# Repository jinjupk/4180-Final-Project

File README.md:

# Contactless Car Unlocking System [ECE 4180 Final Project]

Georgia Institute of Technology \
ECE 4180 (Embedded Systems Design)

Pearl Park \
Lawrence Ro \
Swarna Shah 

## Overview

The Contactless Car Unlocking System allows a user to unlock a car with a specific NFC card instead of using a physical key. In the following demonstration, a Buzzcard student ID is scanned at the sensor location to remotely press the unlock button inside of the car using a 5V relay. The system is powered by the car’s battery which is stepped down to a low enough voltage with a voltage regulator. All components are interfaced through a custom printed circuit board (PCB) and housed in a 3D printed enclosure.

 \

## Components
- MBED LPC1768
- uLCD-144-G2 128 by 128 Smart Color LCD
- 5V relay
- PN532 NFC reader
- Custom PCB
- 3D printed housing

## Hardware

A custom 4-layer PCB includes power management, the microcontroller, and peripherals.

- 4-layer PCB
- LTM8053 Switching Regulator (integrated inductor, 6A max output current)
- Dual LP38692 LDO Voltage Regulator (1A output, separate for servo and microcontroller power)

## Software

The program runs in three separate threads to manage the NFC scanner and uLCD at the same time. 
- Main Thread - Initializes uLCD and NFC scanner threads.
- uLCD Thread - Displays invalid card and card accepted messages according to card scanned.
- NFC Reader - Asks scanner for ID of card scanned, checks it against a known ID, and turns on relay accordingly.

## Video Demo

<div align="center">
  
</div>

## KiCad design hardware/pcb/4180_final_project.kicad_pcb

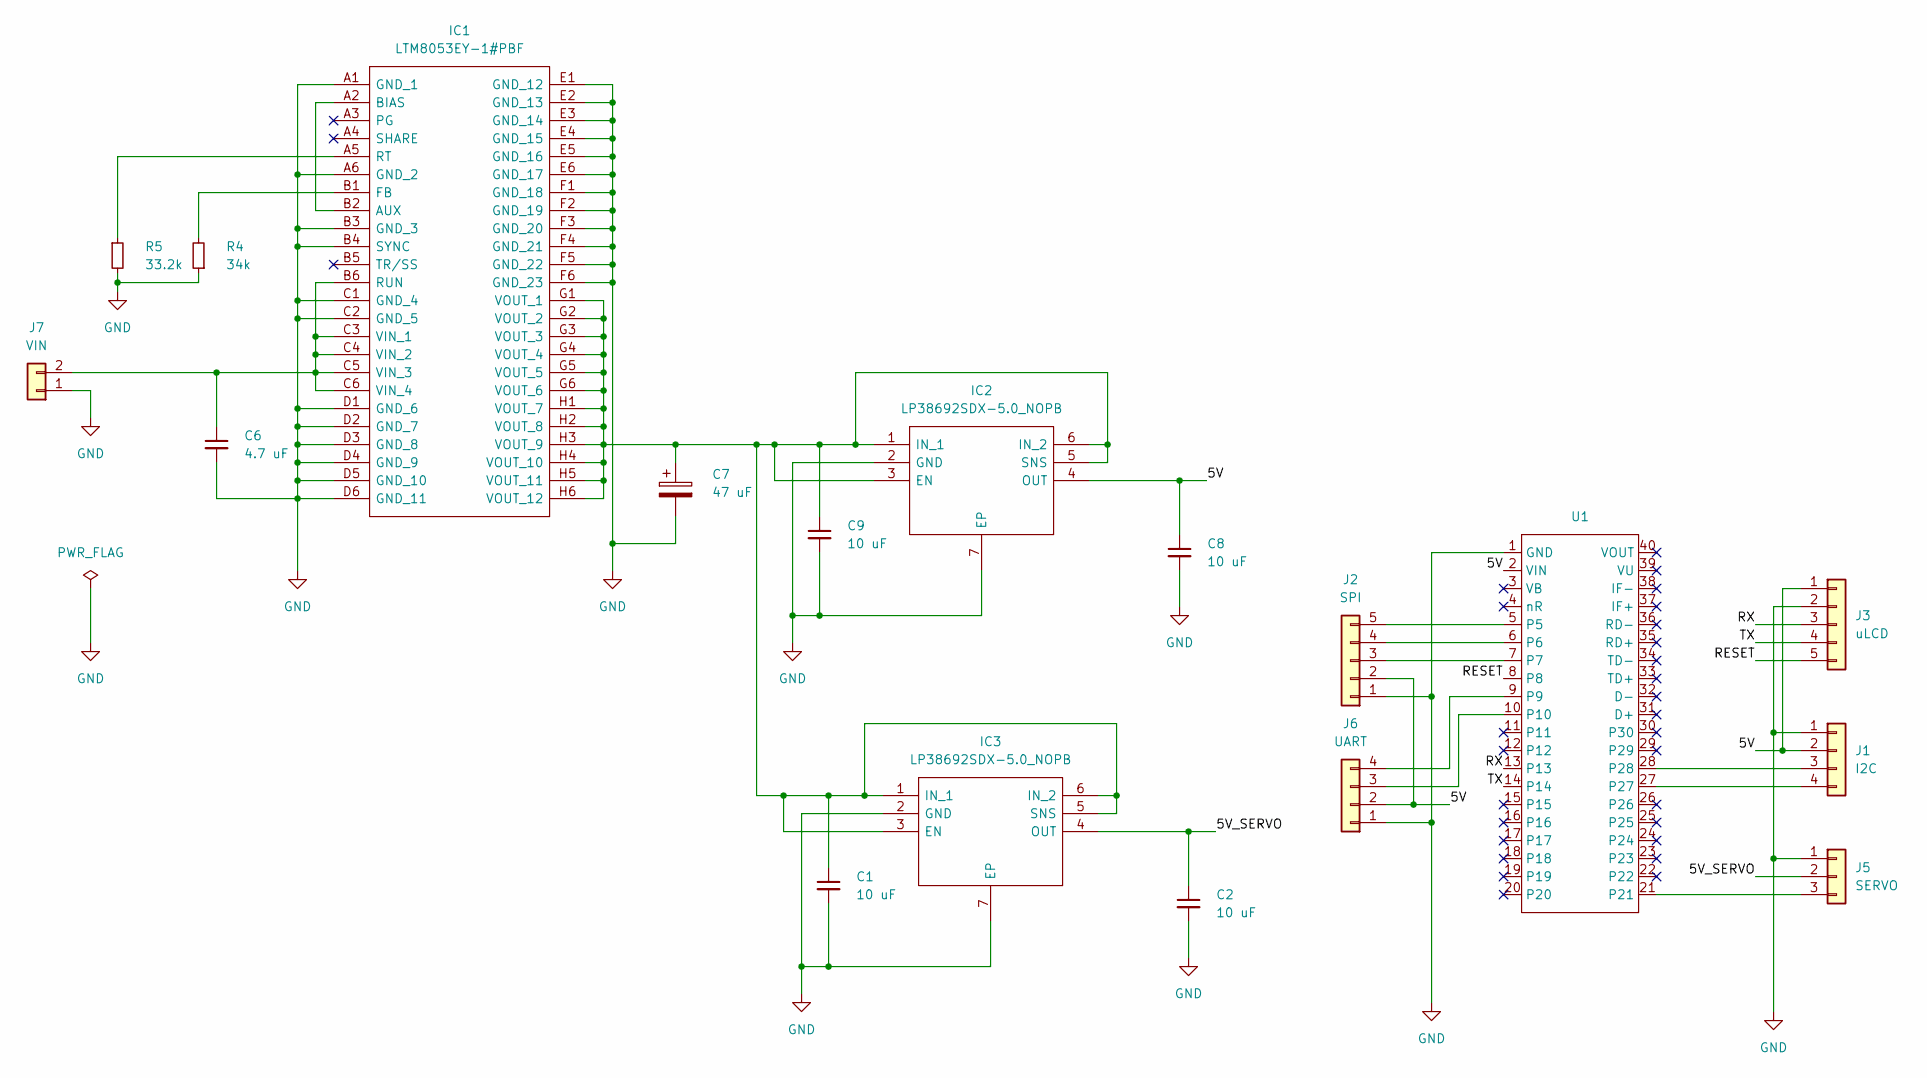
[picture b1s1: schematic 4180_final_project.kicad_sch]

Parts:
C1, C2, C8, C9: 10 uF; C_0603_1608Metric
C6: 4.7 uF; C_1206_3216Metric
C7: 47 uF; C_1210_3225Metric
IC1: LTM8053EY-1#PBF; BGA48C100P6X8_625X900X352; Mouser Part Number 584-LTM8053EY-1#PBF
IC2, IC3: LP38692SDX-5.0_NOPB; SON95P300X300X80-7N; Mouser Part Number 926-LP38692SDX50NOPB
J1: I2C; PinSocket_1x04_P2.54mm_Vertical
J2: SPI; PinSocket_1x05_P2.54mm_Vertical
J3: uLCD; PinSocket_1x05_P2.54mm_Vertical
J5: SERVO; PinSocket_1x03_P2.54mm_Vertical
J6: UART; PinSocket_1x04_P2.54mm_Vertical
J7: VIN; TerminalBlock_bornier-2_P5.08mm
R4: 34k; R_0603_1608Metric
R5: 33.2k; R_0603_1608Metric
U1: DIP-40_900

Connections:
/5V: C8.1, IC2.4 (OUT), J1.2, J2.2, J3.1, J6.2, U1.2 (VIN)
/5V_SERVO: C2.1, IC3.4 (OUT), J5.2
/RESET: J3.5, U1.8
/RX: J3.3, U1.13
/TX: J3.4, U1.14
GND: C1.2, C2.2, C6.2, C7.2, C8.2, C9.2, IC1.A1 (GND_1), IC1.A6 (GND_2), IC1.B3 (GND_3), IC1.B4 (SYNC), IC1.C1 (GND_4), IC1.C2 (GND_5), IC1.D1 (GND_6), IC1.D2 (GND_7), IC1.D3 (GND_8), IC1.D4 (GND_9), IC1.D5 (GND_10), IC1.D6 (GND_11), IC1.E1 (GND_12), IC1.E2 (GND_13), IC1.E3 (GND_14), IC1.E4 (GND_15), IC1.E5 (GND_16), IC1.E6 (GND_17), IC1.F1 (GND_18), IC1.F2 (GND_19), IC1.F3 (GND_20), IC1.F4 (GND_21), IC1.F5 (GND_22), IC1.F6 (GND_23), IC2.2 (GND), IC2.7 (EP), IC3.2 (GND), IC3.7 (EP), J1.1, J2.1, J3.2, J5.1, J6.1, J7.1, R4.1, R5.2, U1.1 (GND)
unnamed: IC1.A2 (BIAS), IC1.B2 (AUX)
unnamed: IC1.B1 (FB), R4.2
unnamed: IC1.A5 (RT), R5.1
unnamed: C6.1, IC1.B6 (RUN), IC1.C3 (VIN_1), IC1.C4 (VIN_2), IC1.C5 (VIN_3), IC1.C6 (VIN_4), J7.2
unnamed: C1.1, C7.1, C9.1, IC1.G1 (VOUT_1), IC1.G2 (VOUT_2), IC1.G3 (VOUT_3), IC1.G4 (VOUT_4), IC1.G5 (VOUT_5), IC1.G6 (VOUT_6), IC1.H1 (VOUT_7), IC1.H2 (VOUT_8), IC1.H3 (VOUT_9), IC1.H4 (VOUT_10), IC1.H5 (VOUT_11), IC1.H6 (VOUT_12), IC2.1 (IN_1), IC2.3 (EN), IC2.5 (SNS), IC2.6 (IN_2), IC3.1 (IN_1), IC3.3 (EN), IC3.5 (SNS), IC3.6 (IN_2)
unnamed: J1.3, U1.28
unnamed: J1.4, U1.27
unnamed: J2.3, U1.7
unnamed: J2.4, U1.6
unnamed: J2.5, U1.5
unnamed: J5.3, U1.21
unnamed: J6.3, U1.10
unnamed: J6.4, U1.9

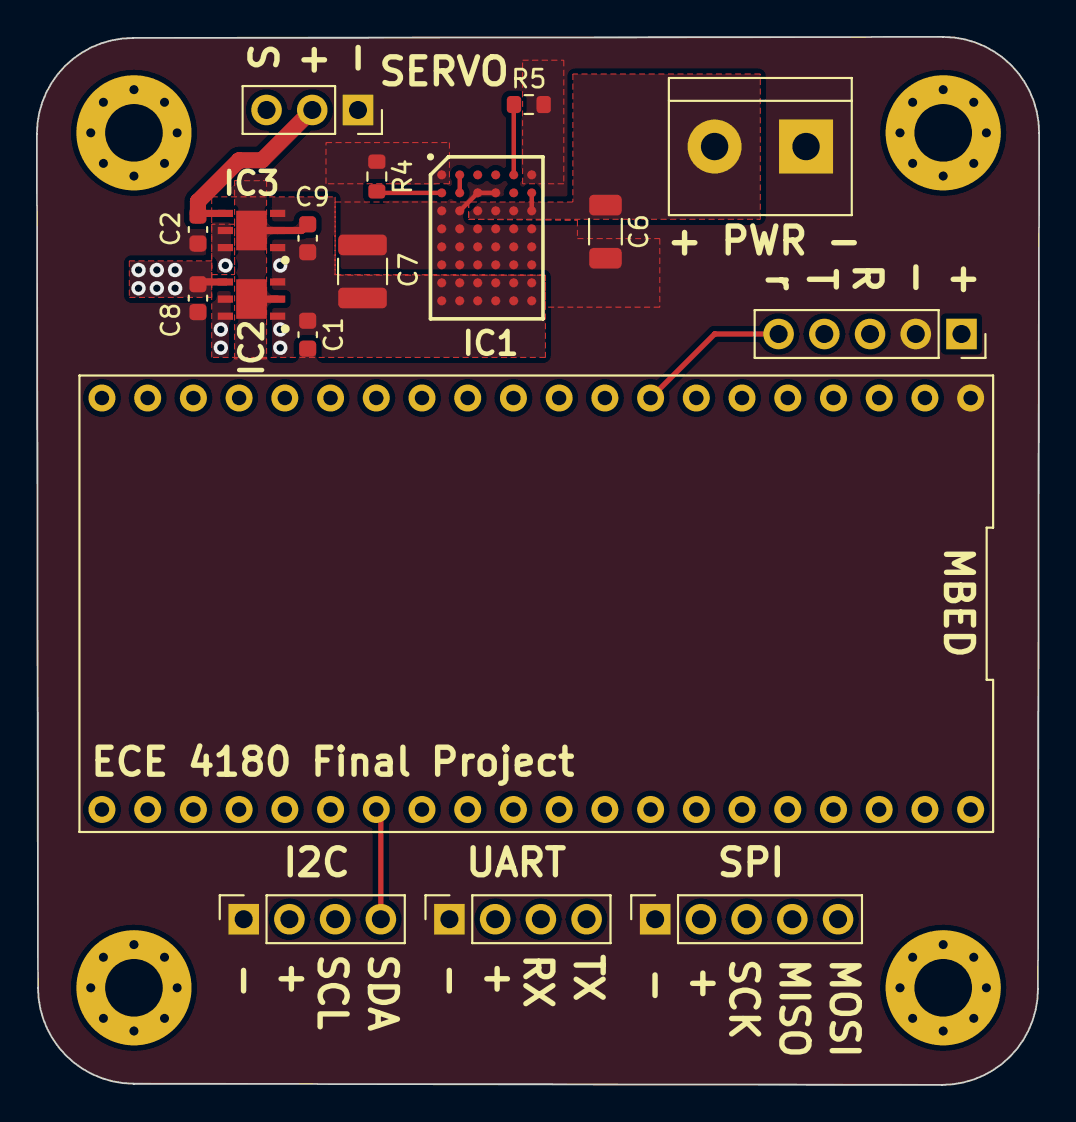
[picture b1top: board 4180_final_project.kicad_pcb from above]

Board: 4 copper layers, 55.7 x 58.2 mm, 18 parts (0 on the bottom side), 19 nets.

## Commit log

2023-12-07 Create PCB_notes
2023-12-07 Create notes
2023-12-07 Update Notes
